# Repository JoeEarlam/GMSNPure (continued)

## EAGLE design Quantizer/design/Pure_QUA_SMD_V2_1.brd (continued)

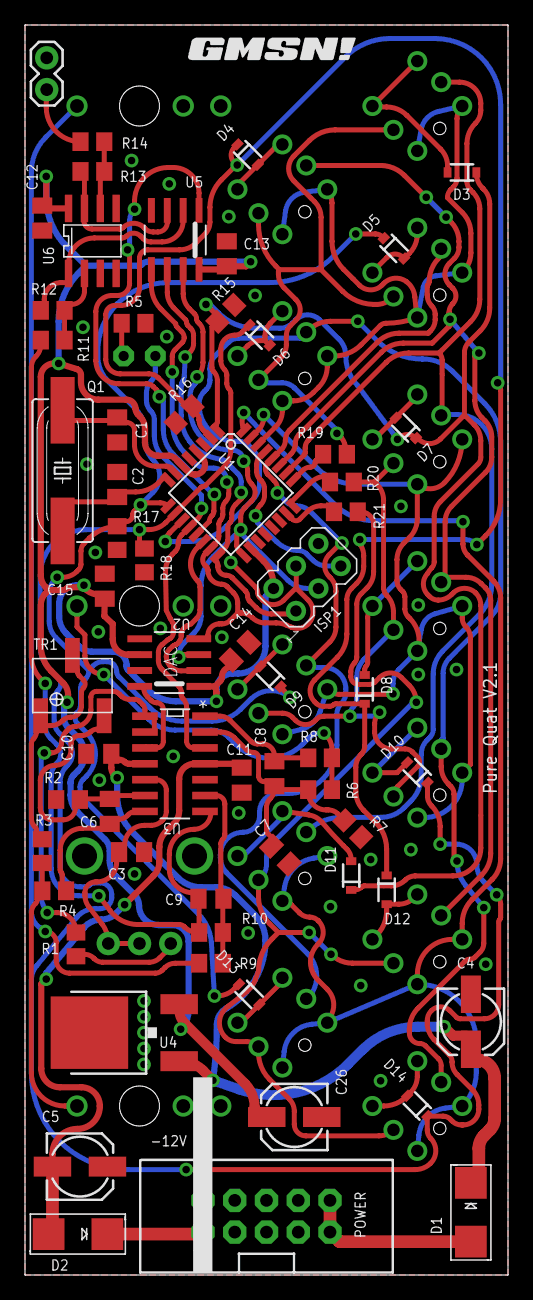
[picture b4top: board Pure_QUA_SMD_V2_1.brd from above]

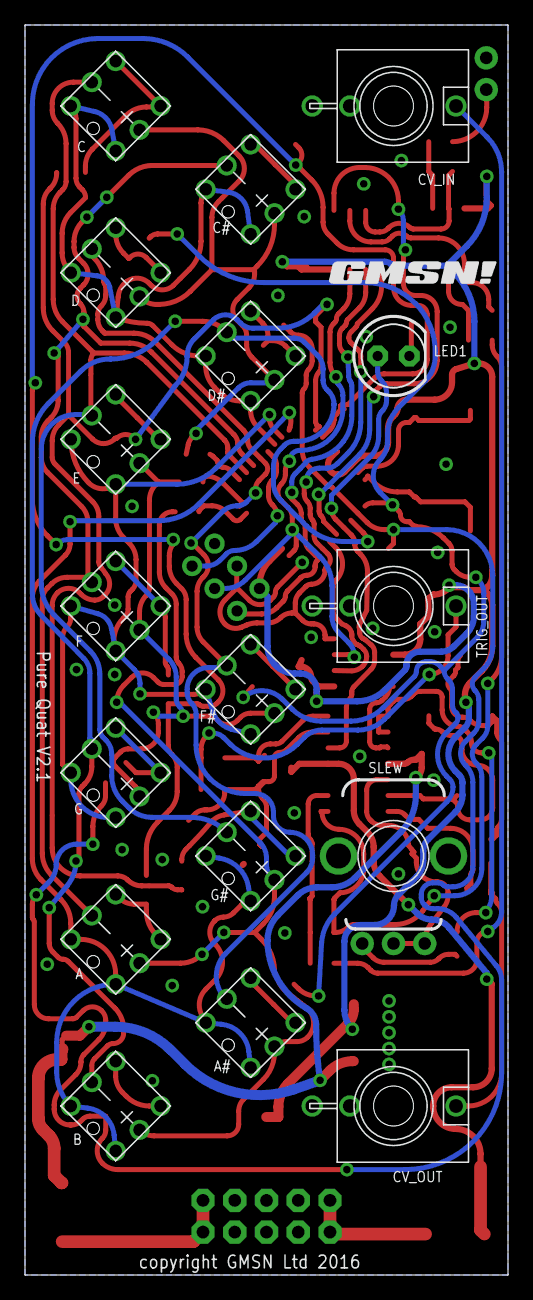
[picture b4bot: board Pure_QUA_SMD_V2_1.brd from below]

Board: 2 copper layers, 38.6 x 100.0 mm, 81 parts (18 on the bottom side), 64 nets.

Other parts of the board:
U$1, U$2: GMSN!_LOGO

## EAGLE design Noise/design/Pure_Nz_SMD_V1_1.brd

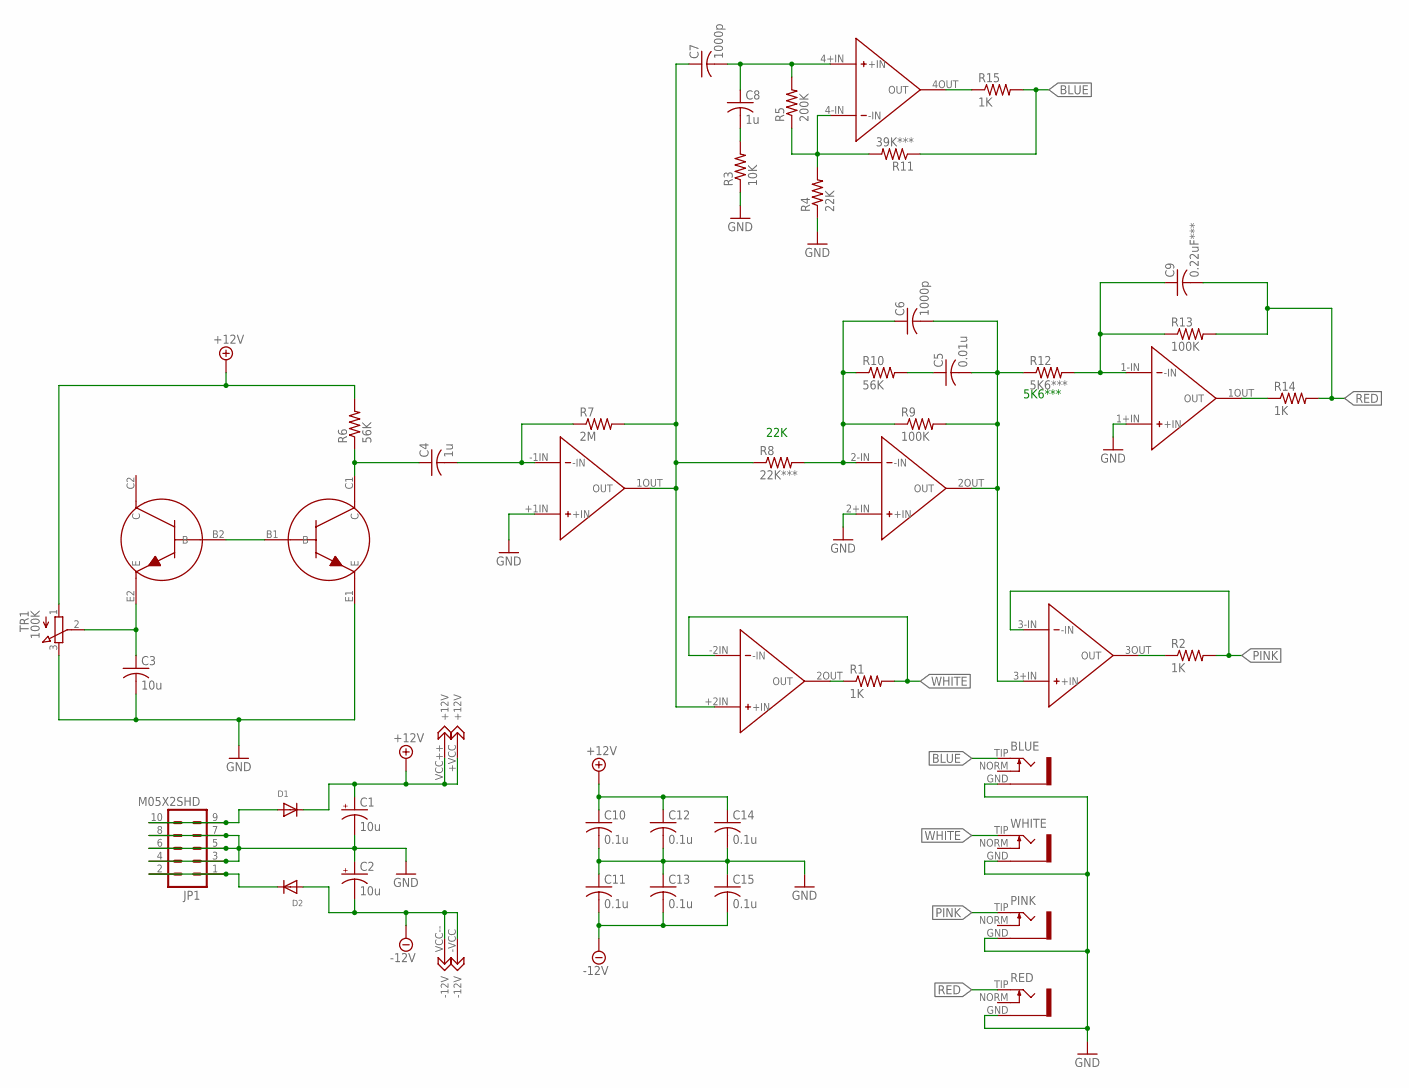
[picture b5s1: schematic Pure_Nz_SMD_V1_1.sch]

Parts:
BLUE: S_JACK
C1, C2: 10u; 153CLV-0505
C3: 10u; C1206K
C4, C8: 1u; C0805K
C5: 0.01u; C0805K
C6, C7: 1000p; C0805K
C9: 0.22uF***; C0805K
C10, C11, C12, C13, C14, C15: 0.1u; C0805K
D1, D2: DIODESMA; SMADIODE
JP1: M05X2SHD; 2X5-SHROUDED
PINK: S_JACK
R1, R2, R14, R15: 1K; R0805
R3: 10K; R0805
R4: 22K; R0805
R5: 200K; R0805
R6, R10: 56K; R0805
R7: 2M; R0805
R8: 22K***; R0805
R9, R13: 100K; R0805
R11: 39K***; R0805
R12: 5K6***; R0805
RED: S_JACK
TR1: 100K; TRIM_3269W
U$1: DUAL_OPAMP
U$6: QUAD_OPAMP
U$9: TRANS_PAIR
WHITE: S_JACK

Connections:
+12V: C1.+, C10.1, C12.1, C14.1, D1.C, R6.2, TR1.1, U$1.+VCC (+12V), U$6.VCC++ (+12V)
-12V: C2.-, C11.2, C13.2, C15.2, D2.A, U$1.-VCC (-12V), U$6.VCC-- (-12V)
BLUE: BLUE.TIP, R11.1, R15.2
GND: BLUE.GND, C1.-, C2.+, C3.2, C10.2, C11.1, C12.2, C13.1, C14.2, C15.1, JP1.3, JP1.4, JP1.5, JP1.6, JP1.7, JP1.8, PINK.GND, R3.1, R4.1, RED.GND, TR1.3, U$1.+1IN (+IN), U$6.1+IN (+IN), U$6.2+IN (+IN), U$9.E1 (E), WHITE.GND
unnamed: R1.1, U$1.2OUT (OUT)
unnamed: R2.1, U$6.3OUT (OUT)
unnamed: C8.2, R3.2
unnamed: C7.2, C8.1, R5.2, U$6.4+IN (+IN)
unnamed: R4.2, R5.1, R11.2, U$6.4-IN (-IN)
unnamed: C9.1, R12.2, R13.1, U$6.1-IN (-IN)
unnamed: R14.1, U$6.1OUT (OUT)
unnamed: D1.A, JP1.9, JP1.10
unnamed: D2.C, JP1.1, JP1.2
unnamed: R15.1, U$6.4OUT (OUT)
unnamed: U$9.B1 (B), U$9.B2 (B)
unnamed: C3.1, TR1.2, U$9.E2 (E)
unnamed: C4.1, R6.1, U$9.C1 (C)
unnamed: C4.2, R7.1, U$1.-1IN (-IN)
unnamed: C6.1, R8.2, R9.1, R10.1, U$6.2-IN (-IN)
unnamed: C5.1, R10.2
unnamed: C7.1, R7.2, R8.1, U$1.1OUT (OUT), U$1.+2IN (+IN)
unnamed: C5.2, C6.2, R9.2, R12.1, U$6.2OUT (OUT), U$6.3+IN (+IN)
PINK: PINK.TIP, R2.2, U$6.3-IN (-IN)
RED: C9.2, R13.2, R14.2, RED.TIP
WHITE: R1.2, U$1.-2IN (-IN), WHITE.TIP

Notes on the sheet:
22K
5K6***

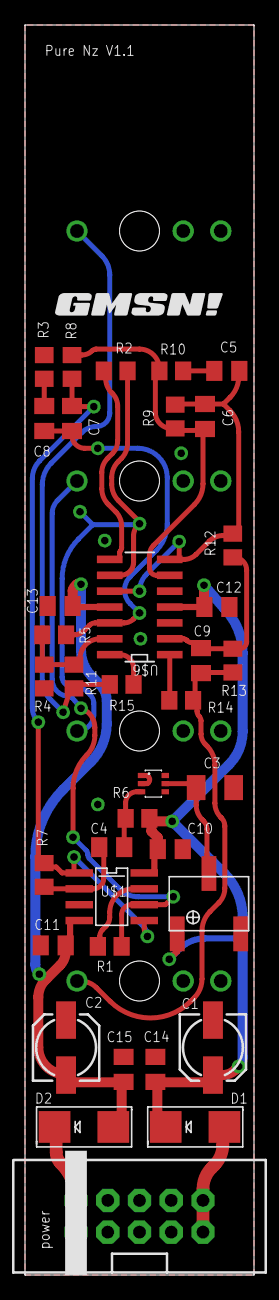
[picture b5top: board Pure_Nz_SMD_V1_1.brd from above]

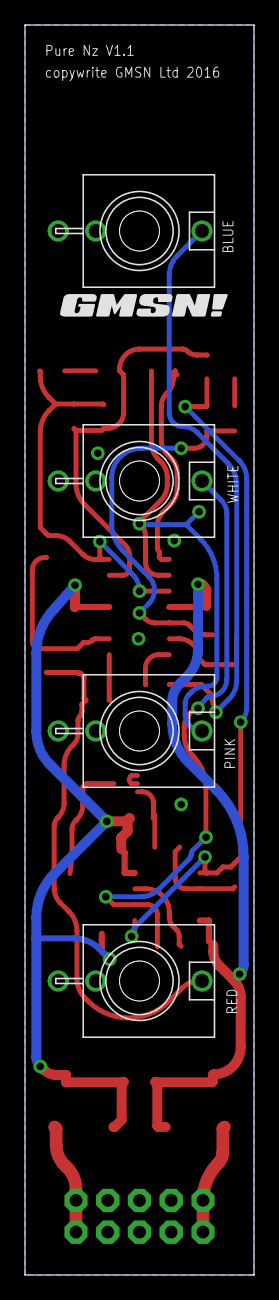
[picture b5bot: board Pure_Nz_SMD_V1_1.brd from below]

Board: 2 copper layers, 18.3 x 100.0 mm, 43 parts (5 on the bottom side), 25 nets.

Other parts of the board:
U$2, U$3: GMSN!_LOGO

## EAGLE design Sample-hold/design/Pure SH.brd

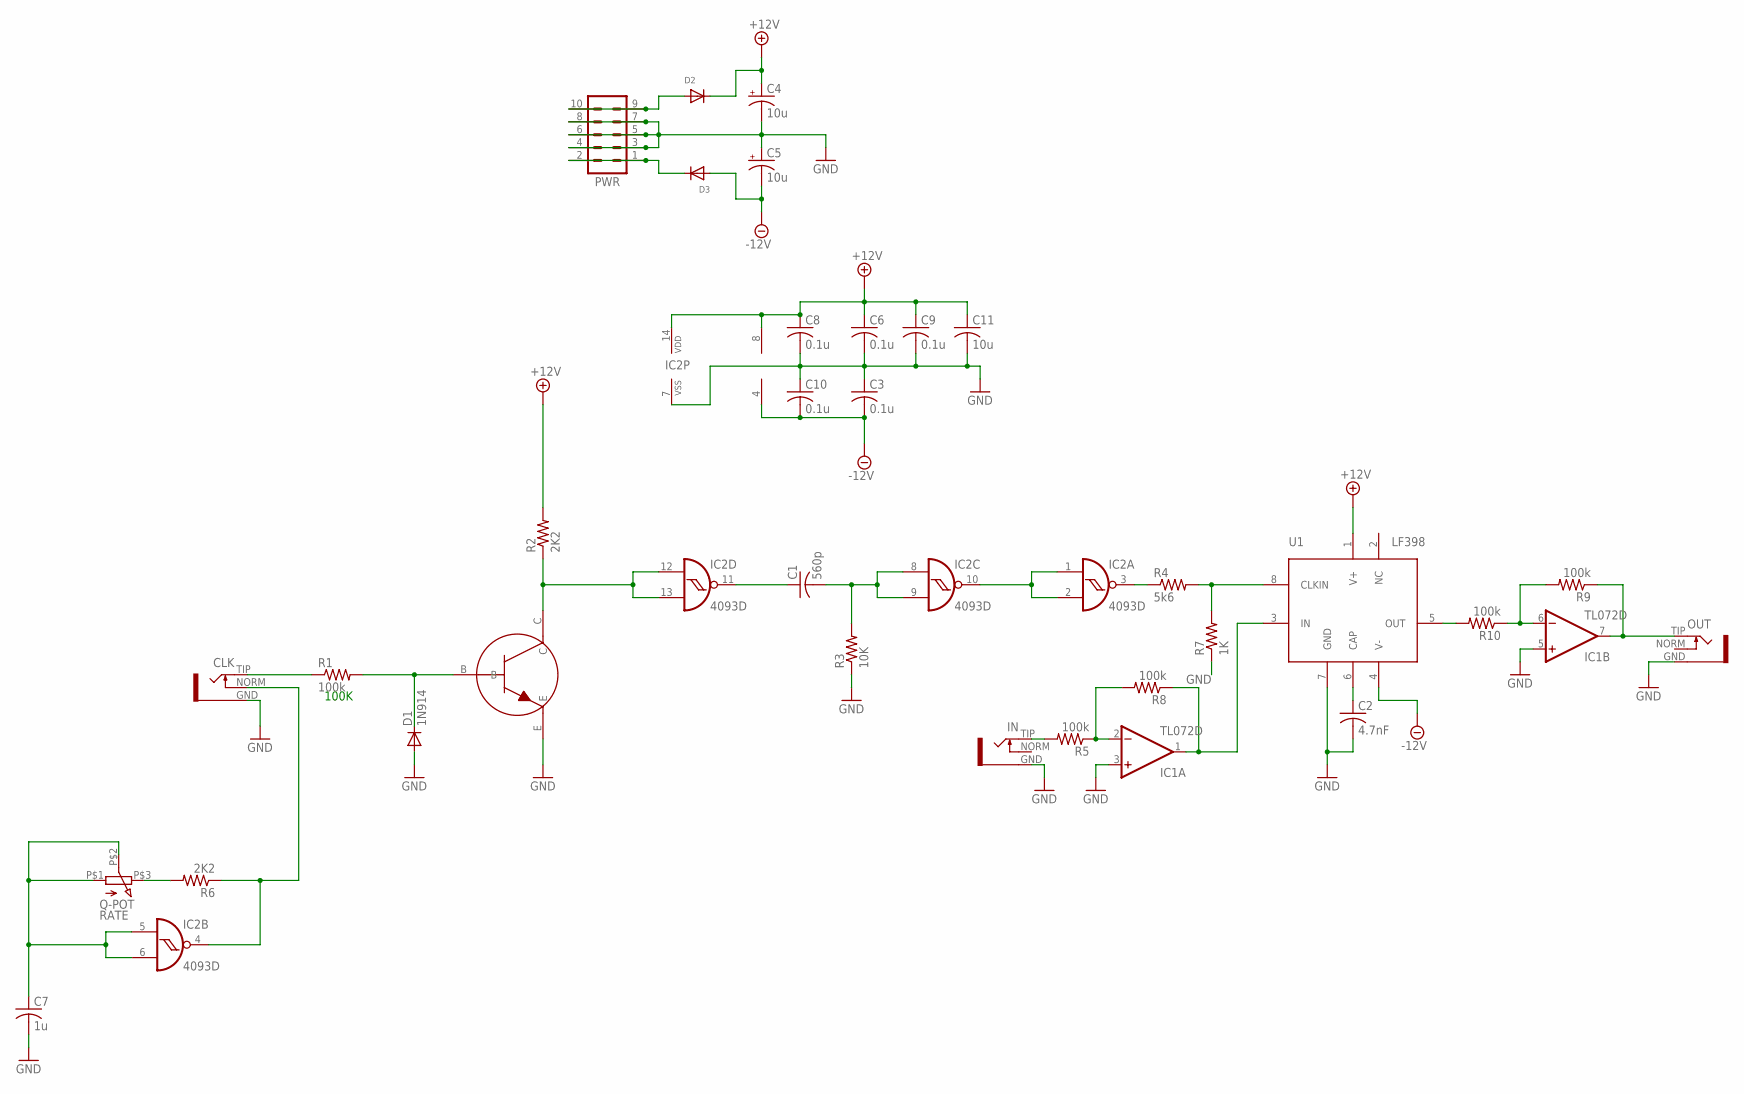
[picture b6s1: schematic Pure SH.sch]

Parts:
C1: 560p; C0805K
C2: 4.7nF; C050-045X075
C3, C6, C8, C9, C10: 0.1u; C0805K
C4, C5: 10u; 153CLV-0505
C7: 1u; C0805K
C11: 10u; C0805K
CLK: S_JACK
D1: 1N914; SOD-323
D2, D3: DIODESMA; SMADIODE
IC1: TL072D; SO08
IC2: 4093D; SO14
IN: S_JACK
OUT: S_JACK
PWR: M05X2SHD; 2X5-SHROUDED
R1, R5, R8, R9, R10: 100k; R0805
R2, R6: 2K2; R0805
R3: 10K; R0805
R4: 5k6; R0805
R7: 1K; R0805
RATE: Q-POT
T1: 3904; TRANSISTOR_SINGLE_N-TYPE
U1: LF398; SOIC--8

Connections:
+12V: C4.+, C6.1, C8.1, C9.1, C11.1, D2.C, IC1.8 (V+), IC2.14 (VDD), R2.2, U1.1 (V+)
-12V: C3.2, C5.-, C10.2, D3.A, IC1.4 (V-), U1.4 (V-)
GND: C2.2, C3.1, C4.-, C5.+, C6.2, C7.2, C8.2, C9.2, C10.1, C11.2, CLK.GND, D1.2 (A), IC1.3 (+IN), IC1.5 (+IN), IC2.7 (VSS), IN.GND, OUT.GND, PWR.3, PWR.4, PWR.5, PWR.6, PWR.7, PWR.8, R3.1, R7.1, T1.E, U1.7 (GND)
unnamed: CLK.TIP, R1.1
unnamed: D1.1 (C), R1.2, T1.B
unnamed: IC2.12 (I0), IC2.13 (I1), R2.1, T1.C
unnamed: C1.1, IC2.11 (O)
unnamed: R4.2, R7.2, U1.8 (CLKIN)
unnamed: C1.2, IC2.8 (I0), IC2.9 (I1), R3.2
unnamed: IC2.1 (I0), IC2.2 (I1), IC2.10 (O)
unnamed: IC2.3 (O), R4.1
unnamed: C2.1, U1.6 (CAP)
unnamed: IN.TIP, R5.2
unnamed: IC1.2 (-IN), R5.1, R8.2
unnamed: R6.2, RATE.P$3 (3)
unnamed: C7.1, IC2.5 (I0), IC2.6 (I1), RATE.P$1 (1), RATE.P$2 (2)
unnamed: CLK.NORM, IC2.4 (O), R6.1
unnamed: IC1.1 (OUT), R8.1, U1.3 (IN)
unnamed: R10.2, U1.5 (OUT)
unnamed: IC1.6 (-IN), R9.2, R10.1
unnamed: IC1.7 (OUT), OUT.TIP, R9.1
unnamed: D2.A, PWR.9, PWR.10
unnamed: D3.C, PWR.1, PWR.2

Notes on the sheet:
100K

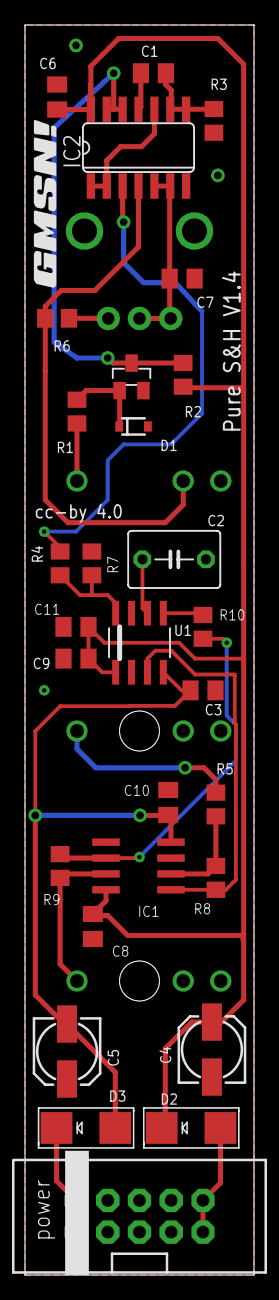
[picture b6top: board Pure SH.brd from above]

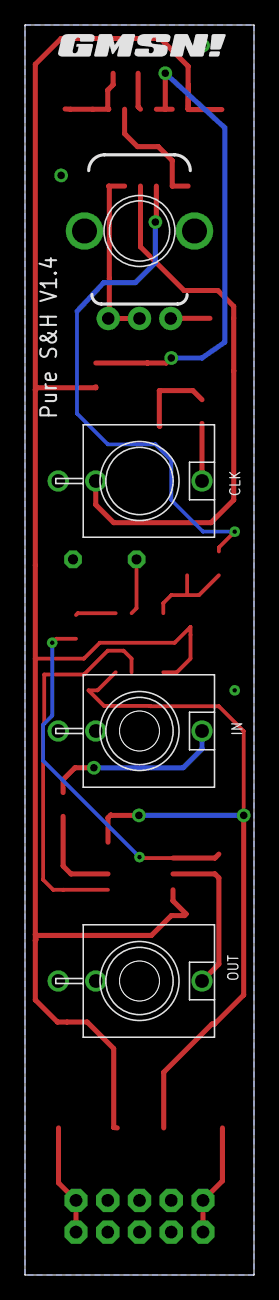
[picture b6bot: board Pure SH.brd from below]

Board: 2 copper layers, 18.3 x 100.0 mm, 35 parts (5 on the bottom side), 23 nets.

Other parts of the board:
U$2, U$3: GMSN!_LOGO

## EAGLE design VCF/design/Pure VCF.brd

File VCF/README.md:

Mouser BoM: http://www.mouser.com/ProjectManager/ProjectDetail.aspx?AccessID=eab9687744

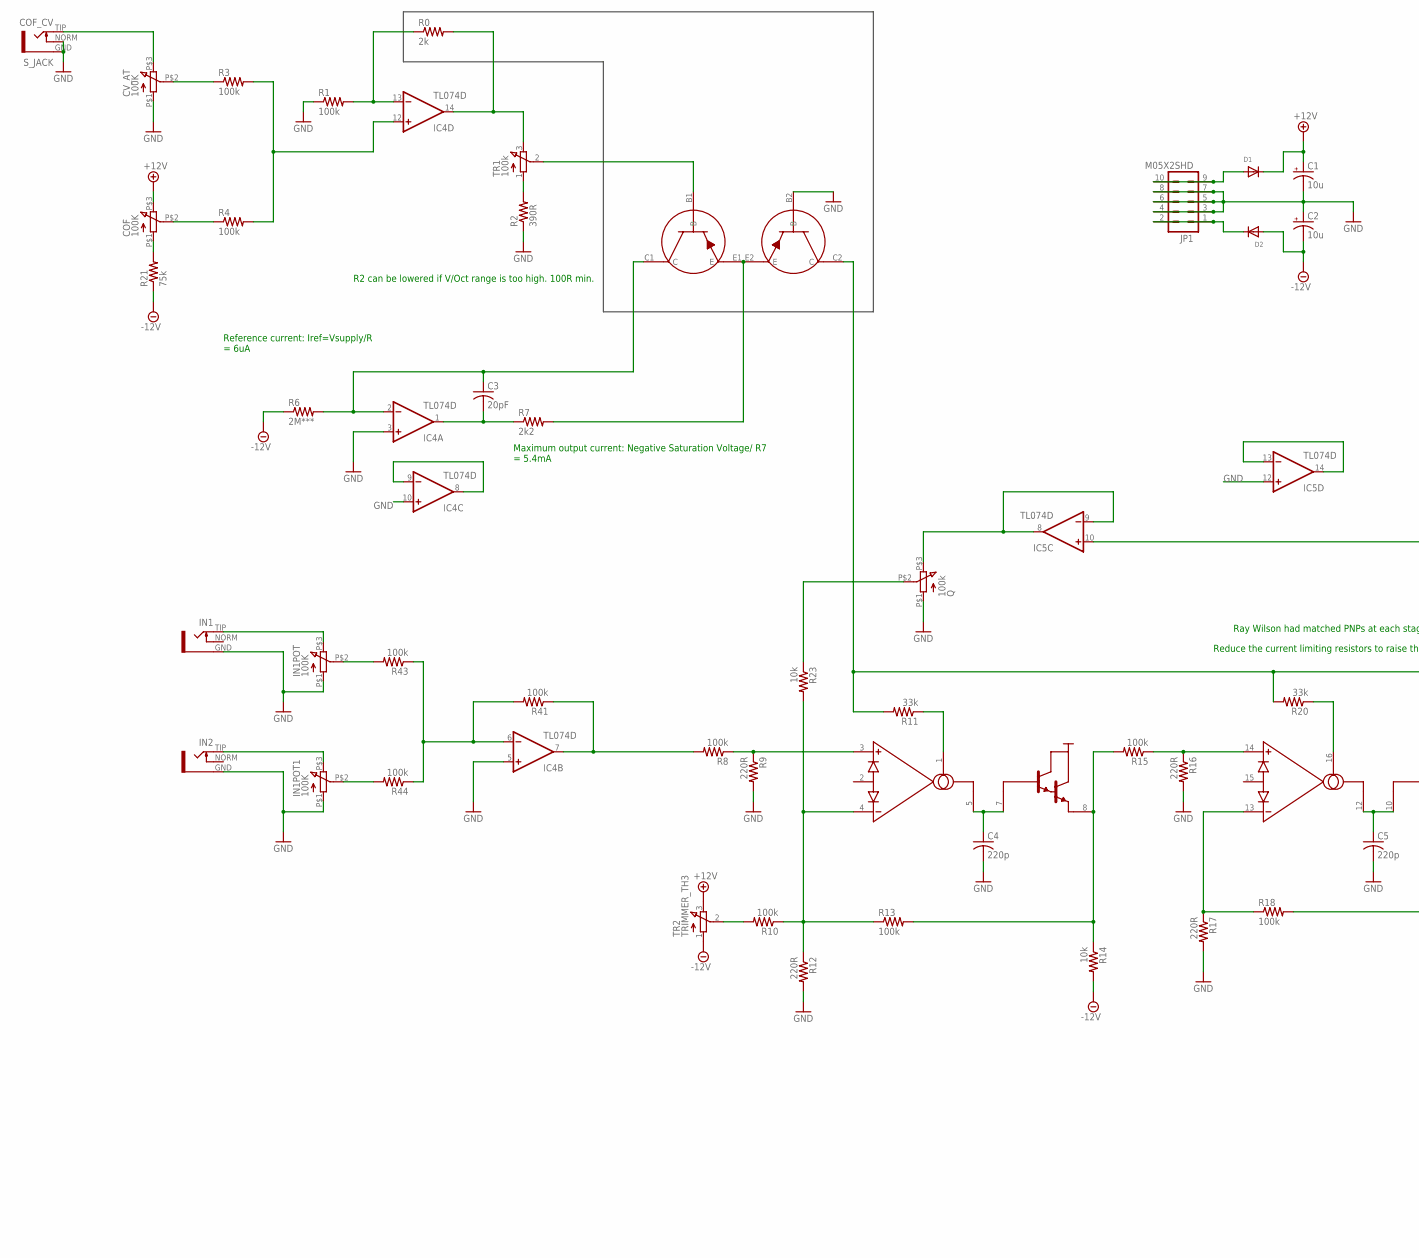
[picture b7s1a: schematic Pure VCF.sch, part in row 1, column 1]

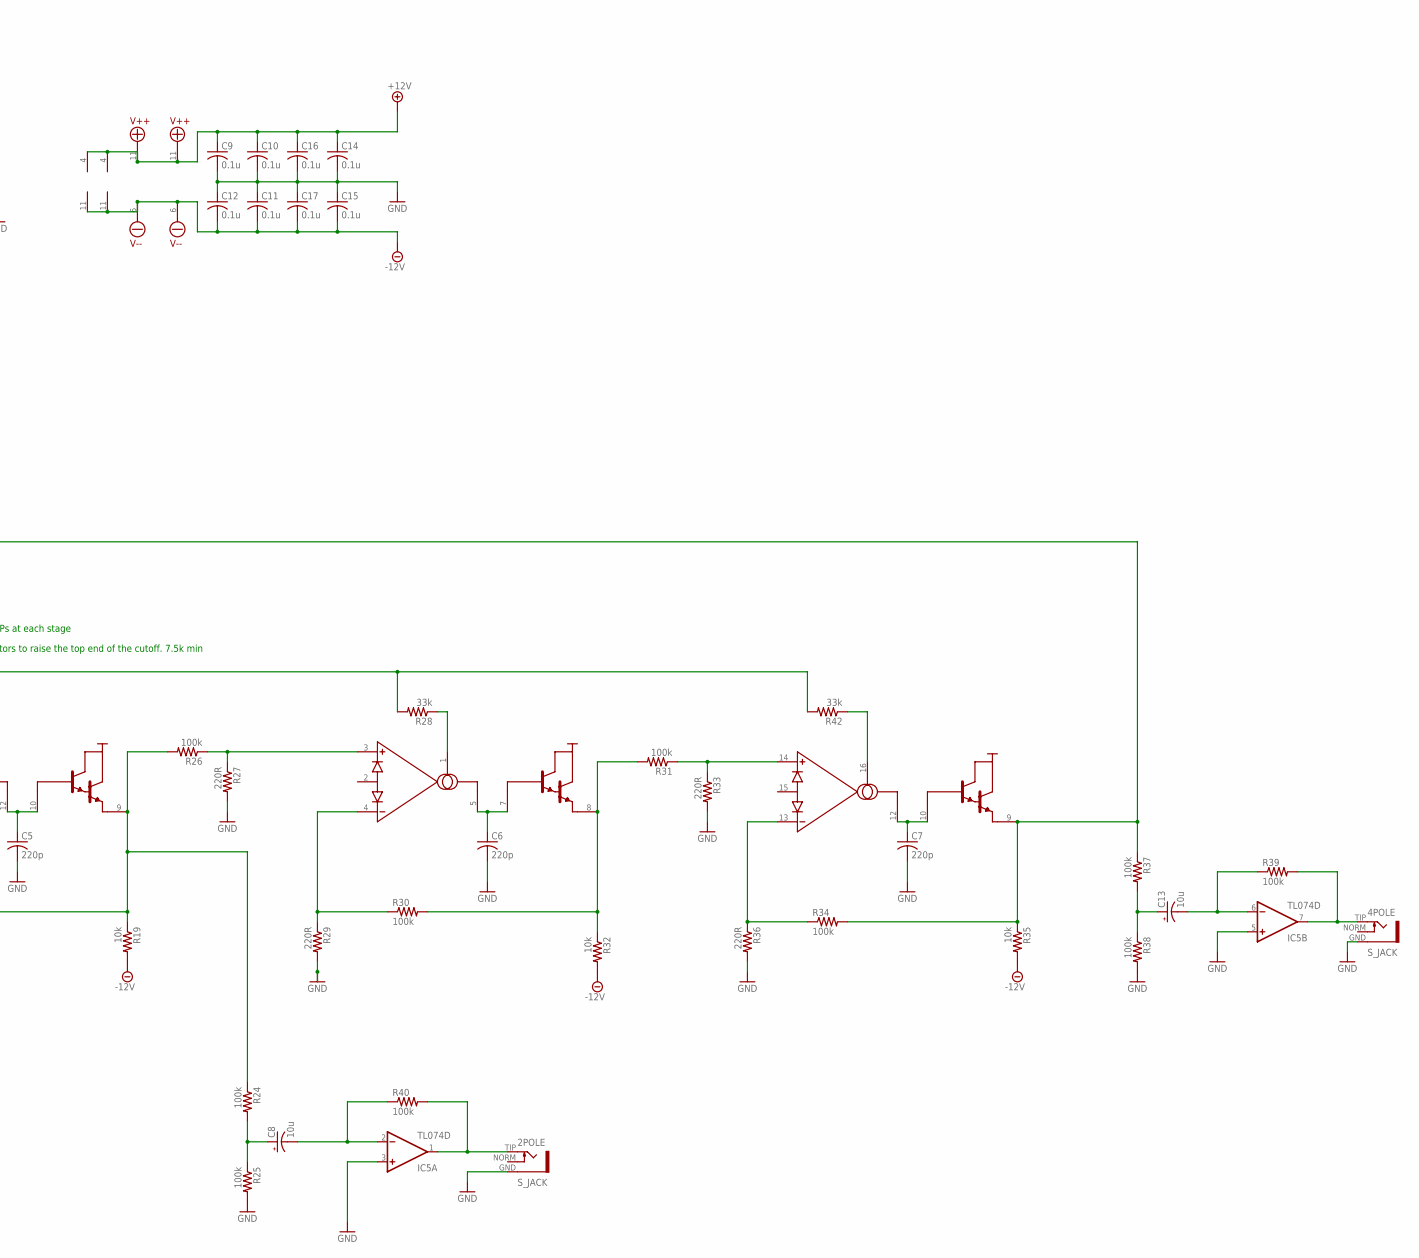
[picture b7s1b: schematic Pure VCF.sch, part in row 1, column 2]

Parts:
2POLE, 4POLE: S_JACK
C1, C2, C8, C13: 10u; 153CLV-0505
C3: 20pF; C0805K
C4, C5, C6, C7: 220p; C050-045X075
C9, C10, C11, C12, C14, C15, C16, C17: 0.1u; C0805K
COF: 100K; POT
COF_CV: S_JACK
CV_AT: 100K; POT
D1, D2: DIODESMA; SMADIODE
IC4, IC5: TL074D; SO14
IN1, IN2: S_JACK
IN1POT, IN1POT1: 100K; POT
JP1: M05X2SHD; 2X5-SHROUDED
Q: 100k; POT
R0: 2k; RESISTOR_TC
R1, R3, R4, R8, R10, R13, R15, R18, R24, R25, R26, R30, R31, R34, R37, R38, R39, R40, R41, R43, R44: 100k; R0805
R2: 390R; R0805
R6: 2M***; R0805
R7: 2k2; R0805
R9, R12, R16, R17, R27, R29, R33, R36: 220R; R0805
R11, R20, R28, R42: 33k; R0805
R14, R19, R23, R32, R35: 10k; R0805
R21: 75k; R0805
T1: TRANS_PAIR_PNP; TRANS_PAIR
TR1: 100k; TRIMMER_TH3
TR2: TRIMMER_TH3
U$3, U$4: LM13700; SOIC-16_BLANK

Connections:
+12V: C1.+, C9.1, C10.1, C14.1, C16.1, COF.P$3 (3), D1.C, IC4.4 (V+), IC5.4 (V+), TR2.3, U$3.11 (V++), U$4.11 (V++)
-12V: C2.-, C11.2, C12.2, C15.2, C17.2, D2.A, IC4.11 (V-), IC5.11 (V-), R6.1, R14.2, R19.2, R21.1, R32.2, R35.2, TR2.1, U$3.6 (V--), U$4.6 (V--)
GND: 2POLE.GND, 4POLE.GND, C1.-, C2.+, C4.2, C5.2, C6.2, C7.2, C9.2, C10.2, C11.1, C12.1, C14.2, C15.1, C16.2, C17.1, COF_CV.GND, COF_CV.NORM, CV_AT.P$1 (1), IC4.3 (+IN), IC4.5 (+IN), IC4.10 (+IN), IC5.3 (+IN), IC5.5 (+IN), IC5.12 (+IN), IN1.GND, IN1POT.P$1 (1), IN1POT1.P$1 (1), IN2.GND, JP1.3, JP1.4, JP1.5, JP1.6, JP1.7, JP1.8, Q.P$1 (1), R1.1, R2.1, R9.2, R12.2, R16.2, R17.2, R25.2, R27.2, R29.2, R33.2, R36.2, R38.2, T1.B2 (B)
unnamed: C5.1, U$3.10 (BUF-IN_2), U$3.12 (OUT)
unnamed: T1.B1 (B), TR1.2
unnamed: R2.2, TR1.1
unnamed: R10.1, R12.1, R13.1, R23.2, U$3.4 (IN-)
unnamed: IC4.14 (OUT), R0.2, TR1.3
unnamed: IC4.13 (-IN), R0.1, R1.2
unnamed: COF_CV.TIP, CV_AT.P$3 (3)
unnamed: IC4.12 (+IN), R3.2, R4.2
unnamed: CV_AT.P$2 (2), R3.1
unnamed: COF.P$2 (2), R4.1
unnamed: C3.1, IC4.2 (-IN), R6.2, T1.C1 (C)
unnamed: C3.2, IC4.1 (OUT), R7.1
unnamed: R11.1, U$3.1 (BIAS-IN)
unnamed: R7.2, T1.E1 (E), T1.E2 (E)
unnamed: IC4.6 (-IN), R41.2, R43.1, R44.1
unnamed: R18.2, R19.1, R24.1, R26.2, U$3.9 (BUF-OUT_2)
unnamed: R8.1, R9.1, U$3.3 (IN+)
unnamed: C8.-, IC5.2 (-IN), R40.1
unnamed: Q.P$2 (2), R23.1
unnamed: IC5.8 (OUT), IC5.9 (-IN), Q.P$3 (3)
unnamed: C13.-, IC5.6 (-IN), R39.1
unnamed: R20.1, U$3.16 (BIAS-IN)
unnamed: R15.1, R16.1, U$3.14 (IN+)
unnamed: R17.1, R18.1, U$3.13 (IN-)
unnamed: COF.P$1 (1), R21.2
unnamed: C8.+, R24.2, R25.1
unnamed: C4.1, U$3.5 (OUT), U$3.7 (BUF-IN_2)
unnamed: R13.2, R14.1, R15.2, U$3.8 (BUF-OUT_2)
unnamed: R26.1, R27.1, U$4.3 (IN+)
unnamed: 2POLE.TIP, IC5.1 (OUT), R40.2
unnamed: R42.1, U$4.16 (BIAS-IN)
unnamed: IC4.7 (OUT), R8.2, R41.1
unnamed: R29.1, R30.1, U$4.4 (IN-)
unnamed: R11.2, R20.2, R28.2, R42.2, T1.C2 (C)
unnamed: C13.+, R37.2, R38.1
unnamed: IC5.13 (-IN), IC5.14 (OUT)
unnamed: D1.A, JP1.9, JP1.10
unnamed: IC4.8 (OUT), IC4.9 (-IN)
unnamed: R34.1, R36.1, U$4.13 (IN-)
unnamed: 4POLE.TIP, IC5.7 (OUT), R39.2
unnamed: R31.1, R33.1, U$4.14 (IN+)
unnamed: R30.2, R31.2, R32.1, U$4.8 (BUF-OUT_2)
unnamed: IC5.10 (+IN), R34.2, R35.1, R37.1, U$4.9 (BUF-OUT_2)
unnamed: IN1.TIP, IN1POT.P$3 (3)
unnamed: IN1POT1.P$3 (3), IN2.TIP
unnamed: D2.C, JP1.1, JP1.2
unnamed: IN1POT.P$2 (2), R43.2
unnamed: R10.2, TR2.2
unnamed: IN1POT1.P$2 (2), R44.2
unnamed: C6.1, U$4.5 (OUT), U$4.7 (BUF-IN_2)
unnamed: C7.1, U$4.10 (BUF-IN_2), U$4.12 (OUT)
unnamed: R28.1, U$4.1 (BIAS-IN)

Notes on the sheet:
Reference current: Iref=Vsupply/R = 6uA
Maximum output current: Negative Saturation Voltage/ R7 = 5.4mA
R2 can be lowered if V/Oct range is too high. 100R min.
Reduce the current limiting resistors to raise the top end of the cutoff. 7.5k min
Ray Wilson had matched PNPs at each stage

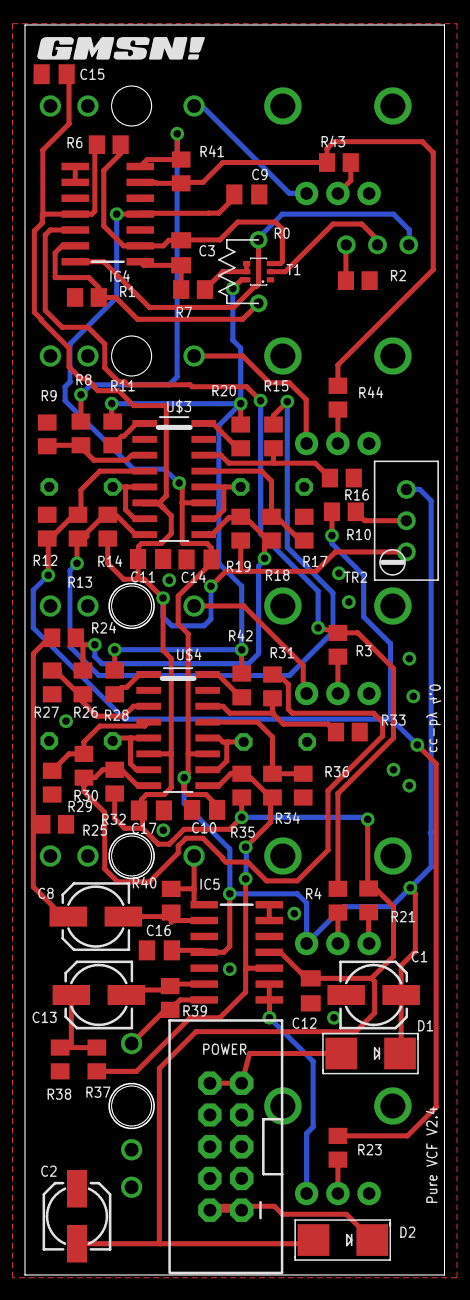
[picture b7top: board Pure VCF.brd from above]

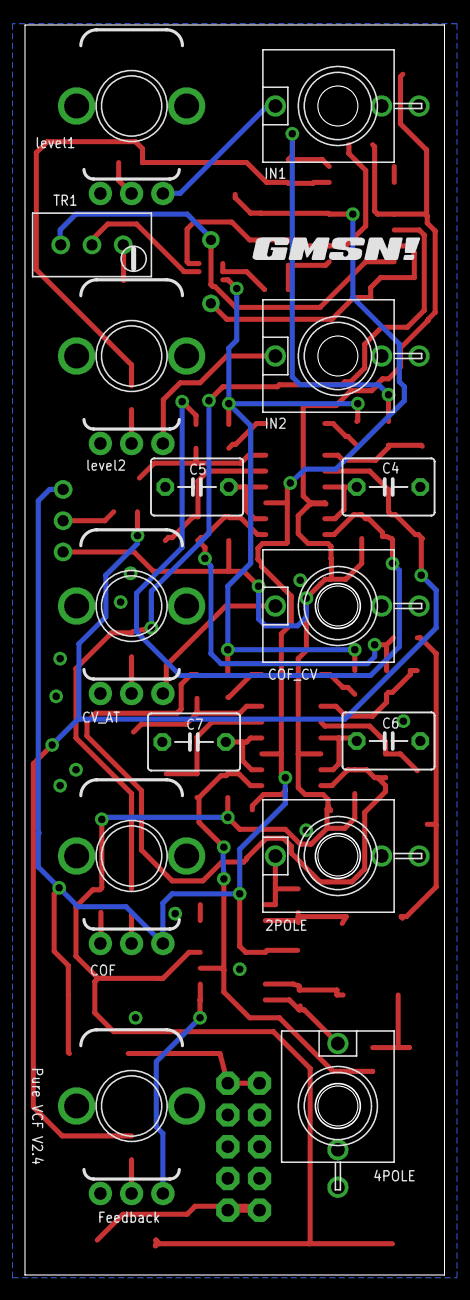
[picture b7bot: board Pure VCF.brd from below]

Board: 2 copper layers, 33.6 x 100.0 mm, 82 parts (16 on the bottom side), 55 nets.

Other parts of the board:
U$1, U$2: GMSN!_LOGO

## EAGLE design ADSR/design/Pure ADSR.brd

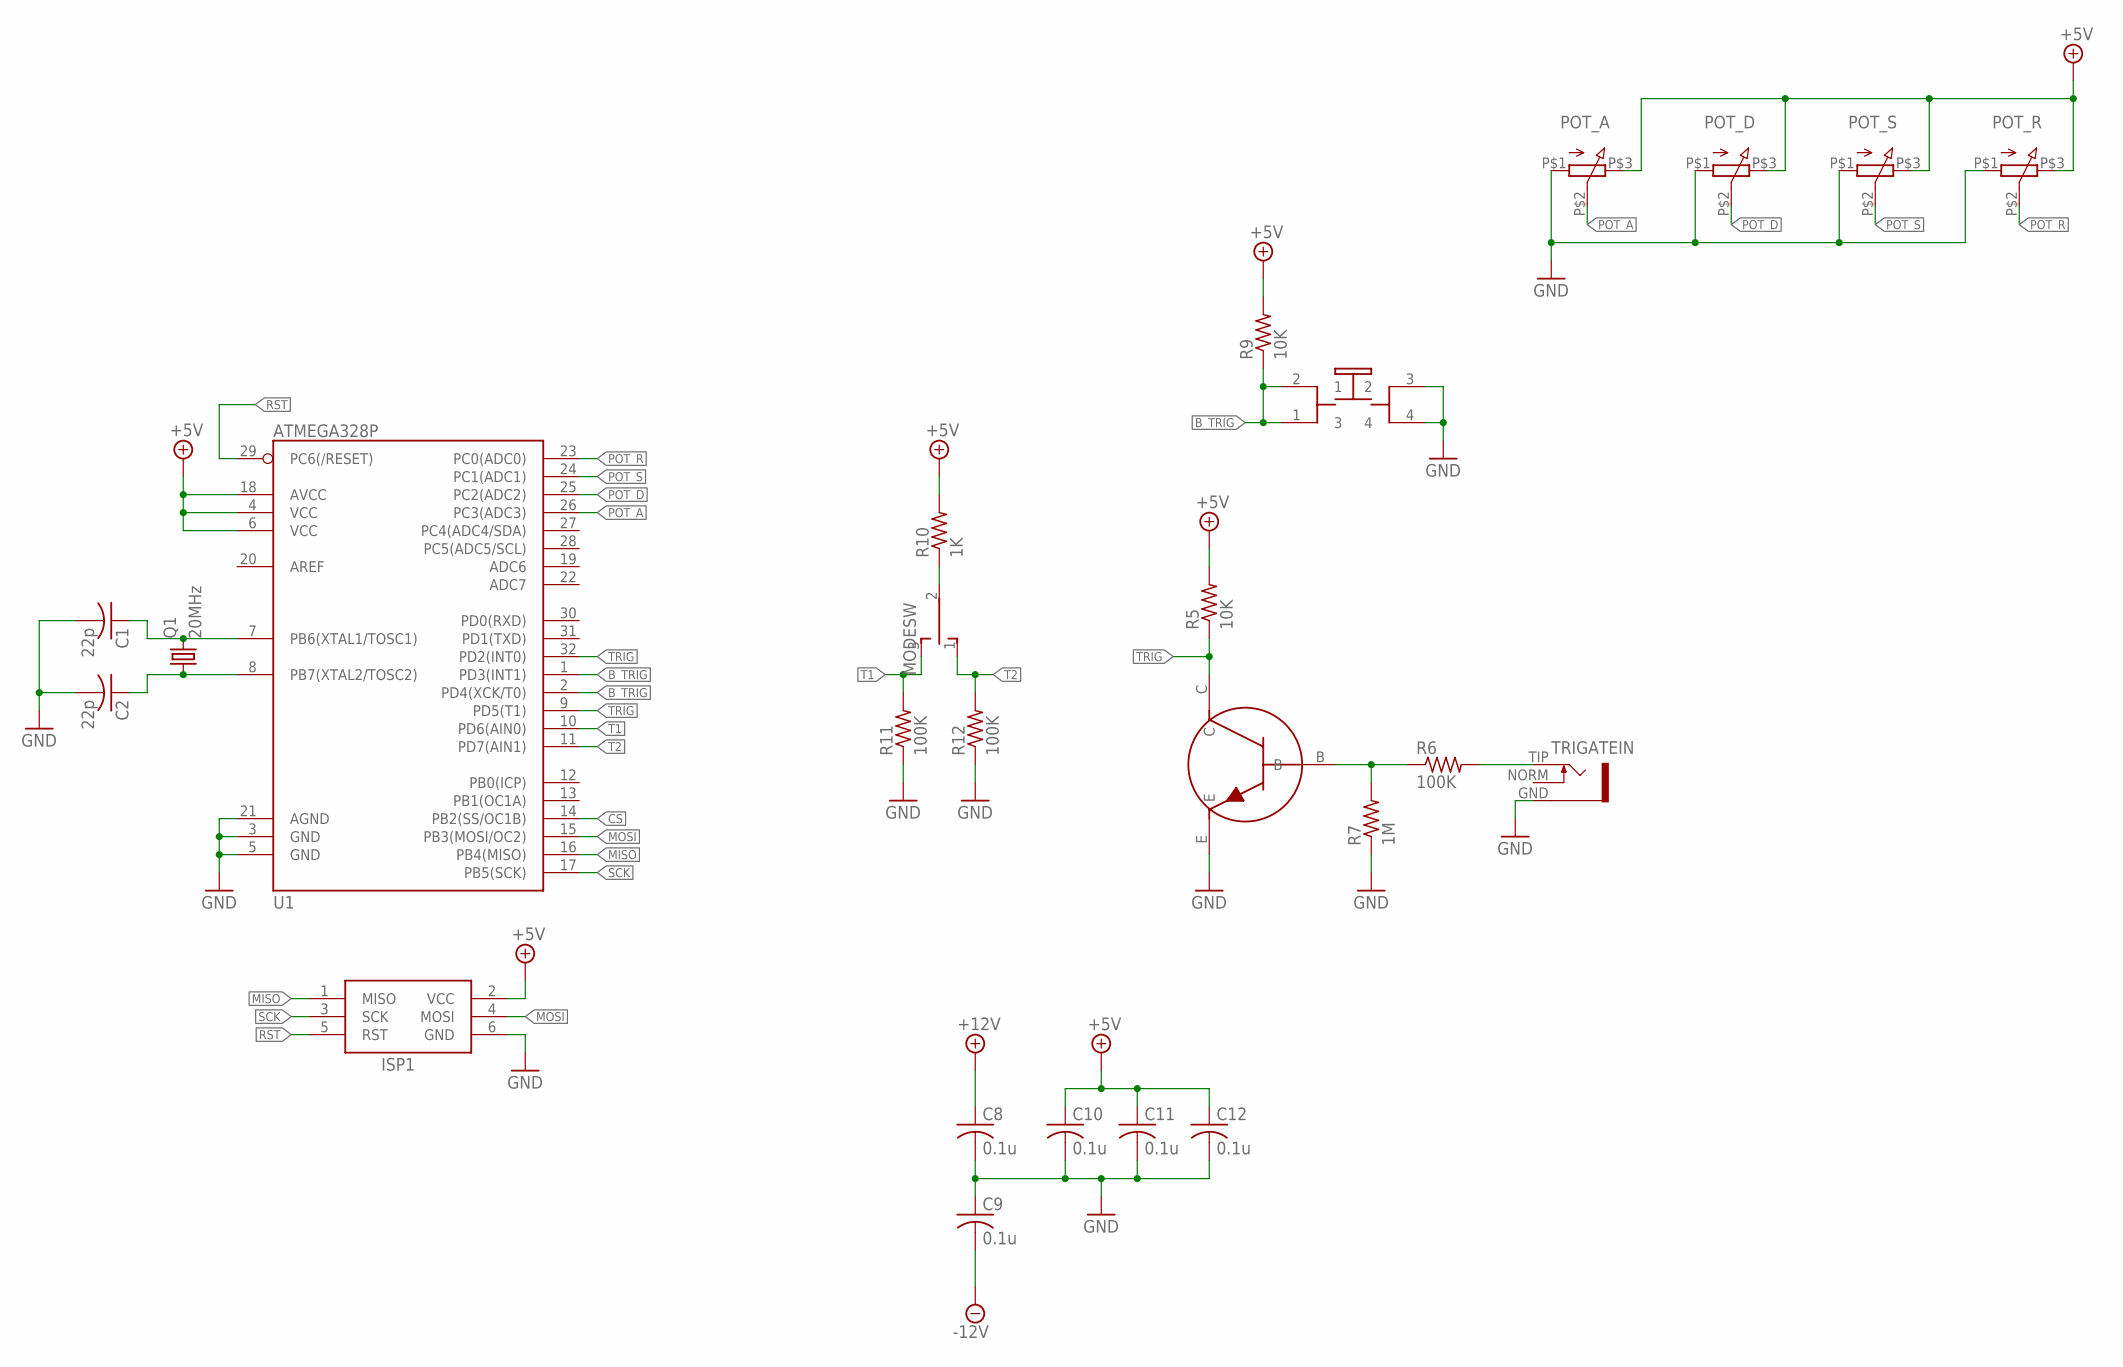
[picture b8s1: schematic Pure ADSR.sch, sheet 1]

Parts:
BUT: PB6149L-5; PB6149L
C1, C2: 22p; C0805K
C8, C9, C10, C11, C12: 0.1u; C0805K
ISP1: AVRISP-6; AVRISP
MODESW: TOGGLE_ON_OFF_ON
POT_A: Q-POT
POT_D: Q-POT
POT_R: Q-POT
POT_S: Q-POT
Q1: 20MHz; HC49UP
R5, R9: 10K; R0805
R6, R11, R12: 100K; R0805
R7: 1M; R0805
R10: 1K; R0805
T1: 2N3904; TRANSISTOR_SINGLE_N-TYPE
TRIGATEIN: S_JACK
U1: ATMEGA328P; TQFP32-08

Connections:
+5V: C10.1, C11.1, C12.1, ISP1.2 (VCC), POT_A.P$3 (3), POT_D.P$3 (3), POT_R.P$3 (3), POT_S.P$3 (3), R5.2, R9.2, R10.2, U1.4 (VCC), U1.6 (VCC), U1.18 (AVCC); also elsewhere on the board
+12V: C8.1; also elsewhere on the board
-12V: C9.2; also elsewhere on the board
B_TRIG: BUT.1 (3), BUT.2 (1), R9.1, U1.1 (PD3(INT1)), U1.2 (PD4(XCK/T0))
CS: U1.14 (PB2(SS/OC1B)); also elsewhere on the board
GND: BUT.3 (2), BUT.4, C1.2, C2.2, C8.2, C9.1, C10.2, C11.2, C12.2, ISP1.6 (GND), POT_A.P$1 (1), POT_D.P$1 (1), POT_R.P$1 (1), POT_S.P$1 (1), R7.1, R11.1, R12.1, T1.E, TRIGATEIN.GND, U1.3 (GND), U1.5 (GND), U1.21 (AGND); also elsewhere on the board
MISO: ISP1.1 (MISO), U1.16 (PB4(MISO))
MOSI: ISP1.4 (MOSI), U1.15 (PB3(MOSI/OC2)); also elsewhere on the board
unnamed: C1.1, Q1.2, U1.7 (PB6(XTAL1/TOSC1))
unnamed: C2.1, Q1.1, U1.8 (PB7(XTAL2/TOSC2))
unnamed: MODESW.2, R10.1
unnamed: R6.1, R7.2, T1.B
unnamed: R6.2, TRIGATEIN.TIP
POT_A: POT_A.P$2 (2), U1.26 (PC3(ADC3))
POT_D: POT_D.P$2 (2), U1.25 (PC2(ADC2))
POT_R: POT_R.P$2 (2), U1.23 (PC0(ADC0))
POT_S: POT_S.P$2 (2), U1.24 (PC1(ADC1))
RST: ISP1.5 (RST), U1.29 (PC6(/RESET))
SCK: ISP1.3 (SCK), U1.17 (PB5(SCK)); also elsewhere on the board
T1: MODESW.3 (S), R11.2, U1.10 (PD6(AIN0))
T2: MODESW.1 (O), R12.2, U1.11 (PD7(AIN1))
TRIG: R5.1, T1.C, U1.9 (PD5(T1)), U1.32 (PD2(INT0))

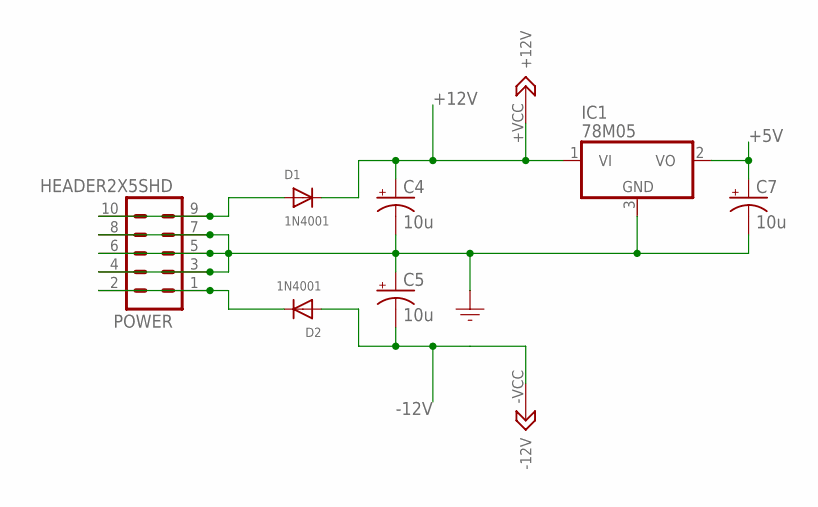
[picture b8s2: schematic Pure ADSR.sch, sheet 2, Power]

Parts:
C4, C5, C7: 10u; 153CLV-0505
D1, D2: 1N4001; SMADIODE
IC1: 78M05; TO252
POWER: HEADER2X5SHD; 2X5-SHROUDED
U2: DUAL_OPAMP

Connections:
+5V: C7.+, IC1.2 (VO); also elsewhere on the board
+12V: C4.+, D1.C, IC1.1 (VI), U2.+VCC (+12V); also elsewhere on the board
-12V: C5.-, D2.A, U2.-VCC (-12V); also elsewhere on the board
GND: C4.-, C5.+, C7.-, IC1.3 (GND), POWER.3, POWER.4, POWER.5, POWER.6, POWER.7, POWER.8; also elsewhere on the board
unnamed: D1.A, POWER.9, POWER.10
unnamed: D2.C, POWER.1, POWER.2

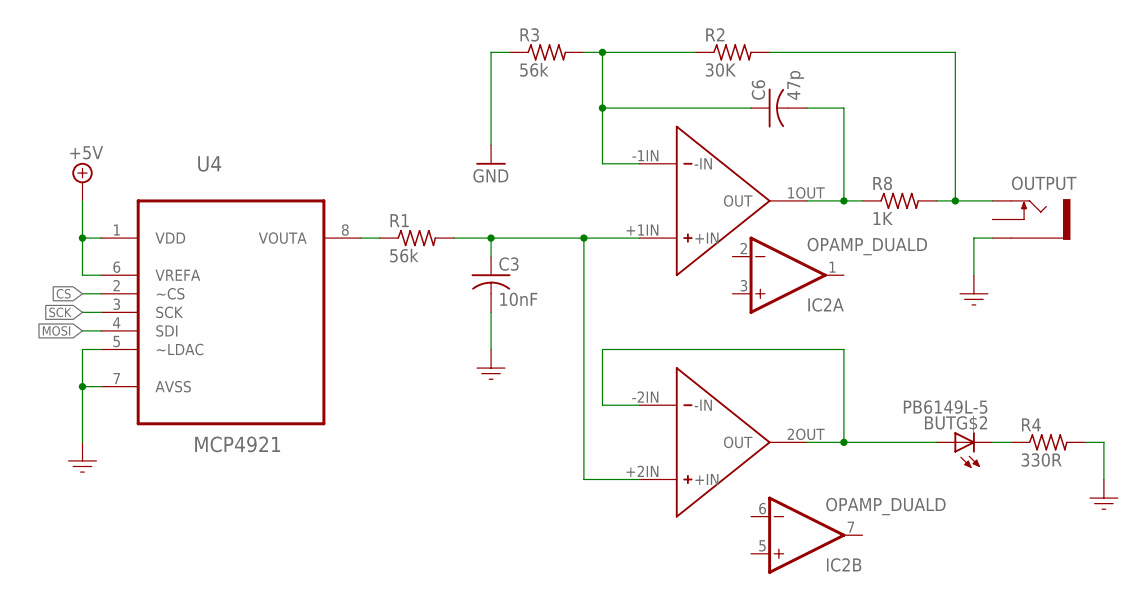
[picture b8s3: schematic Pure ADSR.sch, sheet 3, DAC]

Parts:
BUT: PB6149L-5; PB6149L
C3: 10nF; C0805
C6: 47p; C0805
IC2: OPAMP_DUALD; SO08
OUTPUT: SOCKET_MONO_3.5MMPJ301M-12; PJ301M-12
R1, R3: 56k; R0805
R2: 30K; R0805
R4: 330R; R0805
R8: 1K; R0805
U2: DUAL_OPAMP
U4: MCP4921; SOIC8

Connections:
+5V: U4.1 (VDD), U4.6 (VREFA); also elsewhere on the board
CS: U4.2 (~CS); also elsewhere on the board
GND: C3.2, OUTPUT.GND (SLEEVE), R3.1, R4.2, U4.5 (~LDAC), U4.7 (AVSS); also elsewhere on the board
MOSI: U4.4 (SDI); also elsewhere on the board
unnamed: R1.1, U4.8 (VOUTA)
unnamed: C3.1, R1.2, U2.+1IN (+IN), U2.+2IN (+IN)
unnamed: C6.1, R2.1, R3.2, U2.-1IN (-IN)
unnamed: OUTPUT.TIP, R2.2, R8.2
unnamed: BUT.A, U2.2OUT (OUT), U2.-2IN (-IN)
unnamed: BUT.K (C), R4.1
unnamed: C6.2, R8.1, U2.1OUT (OUT)
SCK: U4.3 (SCK); also elsewhere on the board
